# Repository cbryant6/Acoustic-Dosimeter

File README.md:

# Acoustic Dosimeter

A two-device, wireless **acoustic dosimeter** that estimates cumulative sound exposure over time and presents it as a slow-moving analog gauge needle. A compact sensing node performs DSP (RMS + FFT band-energy features + time-weighted integration) and transmits a single exposure metric to a tabletop display with a stepper-driven needle, LED status, and a button.

---

## 1) Overview Slide 

**What it does:** The sensing module continuously samples ambient audio using a MEMS microphone, extracts energy and frequency features (RMS + FFT band energy), and integrates them over time into a single **exposure index**. The display module receives that index wirelessly and visualizes it as a slow-moving gauge needle, with an LED and a single button for reset/calibration.

**Physical features (sketch):** see general sketch above.

---

## 2) Sensor Device (Detailed Sketch + How it Works)

**Role:** Captures ambient audio, runs DSP locally, and transmits a single cumulative exposure metric.

**How it works (high level):**
- The microphone provides a digital I2S audio stream.
- The MCU computes short-window RMS and FFT band energies (e.g., 125 Hz-4 kHz bands), then applies time-weighted integration (accumulate during sustained loudness, decay during quiet).
- The sensor node transmits an exposure value (0-100) periodically (e.g., 1-5 Hz) to the display node.

**Key parts (with part numbers):**
- **MCU / Wireless:** ESP32-C3 (RISC-V Wi-Fi + BLE) (datasheet in `datasheets/ESP32-C3_datasheet_en.pdf`) 
- **Microphone:** INMP441 MEMS I2S microphone (datasheet in `datasheets/INMP441_MEMS_microphone_datasheet.pdf`)
- **Power (battery-only):** 1-cell LiPo + MCP73831 Li-ion/LiPo charger IC (datasheet in `datasheets/MCP73831_LiPo_charger_datasheet_Microchip.pdf`) + AP2112 3.3 V LDO regulator (datasheet in `datasheets/AP2112_LDO_datasheet.pdf`)

**Early technical thoughts (wireless, power, processing):** The sensor module concentrates processing (RMS + FFT + integration) on an ESP32-C3 and uses ESP-NOW (or BLE) to transmit a single exposure metric, minimizing bandwidth and improving privacy by not sending raw audio. Power will be managed with duty-cycling (batching FFT windows + deep sleep between updates) to support battery-only operation.

---

## 3) Display Device (Detailed Sketch + How it Works)

**Role:** Receives the exposure index and visualizes it as an OLED screen as well as an analog needle gauge; provides minimal user interaction.

**How it works (high level):**
- The display MCU receives exposure updates wirelessly.
- A stepper motor drives the needle to a mapped angle (e.g., 0-100 -> 0-180 degrees) with smoothing to avoid jitter.
- A single LED provides status (OK / caution / high exposure) and a button triggers reset or calibration.
- (Optional) OLED can show the numeric exposure value and battery state.

**Key parts (with part numbers):**
- **MCU / Wireless:** ESP32-C3 (same family as sensor node)
- **Stepper motor (needle):** 28BYJ-48 5 V stepper motor (datasheet in `datasheets/28BYJ-48_stepper_motor_datasheet.pdf`)
- **Stepper driver:** ULN2003A Darlington array (datasheet in `datasheets/ULN2003A_datasheet_TI.pdf`)
- **LED:** WS2812B addressable RGB LED (datasheet in `datasheets/WS2812B_RGB_LED_datasheet.pdf`) (can be used as a single LED)
- **Optional display:** SSD1306-based 128x64 OLED over I2C (controller datasheet in `datasheets/SSD1306_OLED_controller_datasheet.pdf`)
- **Button:** 6x6 mm tact switch (generic)

**Early technical thoughts (wireless, power, processing):** The display device keeps processing minimal (receive metric + gauge control + UI), prioritizing stable stepper motion and low power draw. Because the stepper dominates energy use, the display will use a thoughtfully sized larger LiPo and will only move the needle when the metric changes meaningfully.

---

## 4) Communication + Detailed HW/SW Diagram (2 Figures)

### Figure A: Device-to-Device Communication

### Figure B: Detailed System Architecture (HW + SW)

**How the two devices communicate:** The sensing node transmits an exposure index (0-100) over ESP-NOW (or BLE) at a low update rate; the display node acknowledges receipt (optional) and uses smoothing before commanding the stepper position. This keeps the link reliable and low-power while preserving privacy by keeping raw audio on the sensing device.

```
## Datasheets

All component datasheets are stored in the `datasheets/` folder.

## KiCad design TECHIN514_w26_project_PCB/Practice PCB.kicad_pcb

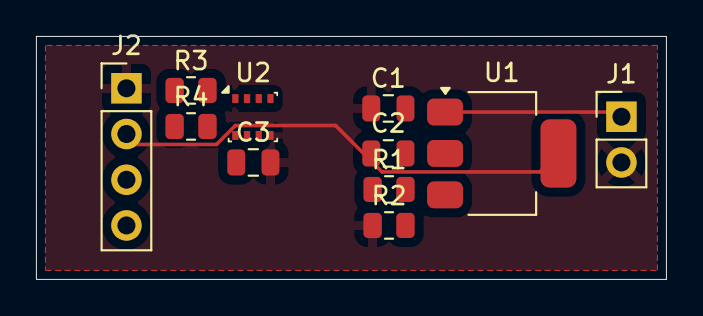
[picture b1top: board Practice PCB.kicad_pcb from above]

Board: 2 copper layers, 35.0 x 13.5 mm, 11 parts (0 on the bottom side), 6 nets.

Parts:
C1, C2, C3: .1; C_0805_2012Metric
J1: Conn_01x02_Pin; PinHeader_1x02_P2.54mm_Vertical
J2: Conn_01x04_Pin; PinHeader_1x04_P2.54mm_Vertical
R1: 240; R_0805_2012Metric
R2: 390; R_0805_2012Metric
R3, R4: 4.7k; R_0805_2012Metric
U1: LM317L_SO8; SOT-223-3_TabPin2
U2: BME280; Bosch_LGA-8_2.5x2.5mm_P0.65mm_ClockwisePinNumbering

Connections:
+3V3: C2.1, C3.1, J2.2, R1.2, R3.1, R4.1, U1.2 (VO), U1.3 (VO), U2.2 (CSB), U2.6 (VDDIO), U2.8 (VDD)
GND: C1.1, C2.2, C3.2, J1.2, J2.1, R2.1, U2.1 (GND), U2.5 (SDO), U2.7 (GND)
unnamed: C1.2, J1.1, U1.1 (VI)
unnamed: J2.3, R4.2, U2.3 (SDI)
unnamed: J2.4, R3.2, U2.4 (SCK)
unnamed: R1.1, R2.2

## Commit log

2026-01-20 Add files via upload
    Initial system architecture and component datasheets
2026-01-30 Schematics
2026-01-30 Create system_architecture folder
2026-01-30 README is here on purpose
2026-01-30 Practice PCB Upload
2026-01-30 Adding Manufacturer Files
2026-02-08 Add excel link for Bat_Est_Excel
2026-03-02 Add introductory code section to README
2026-03-02 Add intro code snippet to README
    Added introductory code snippet for ESP-NOW communication.
2026-03-16 Adding updated schematics
2026-03-16 Code for both devices
2026-04-29 Revise overview and sensor device sections in README
    Updated README to improve clarity and formatting of sections.
2026-04-29 Replace images in README with updated links
    Updated images in README with new links and removed old image syntax.
2026-04-29 Update section titles and add detailed sketches
2026-04-29 Replace general concept sketch image
    Updated image in README with a new URL.
2026-05-01 Remove first image from Display Device section
    Removed the first image from the Display Device section.
2026-05-01 Add additional image to README.md
2026-05-01 Device Code
2026-05-04 Add new image to README
2026-05-04 Remove intro code from README
    Removed introductory code section from README.
